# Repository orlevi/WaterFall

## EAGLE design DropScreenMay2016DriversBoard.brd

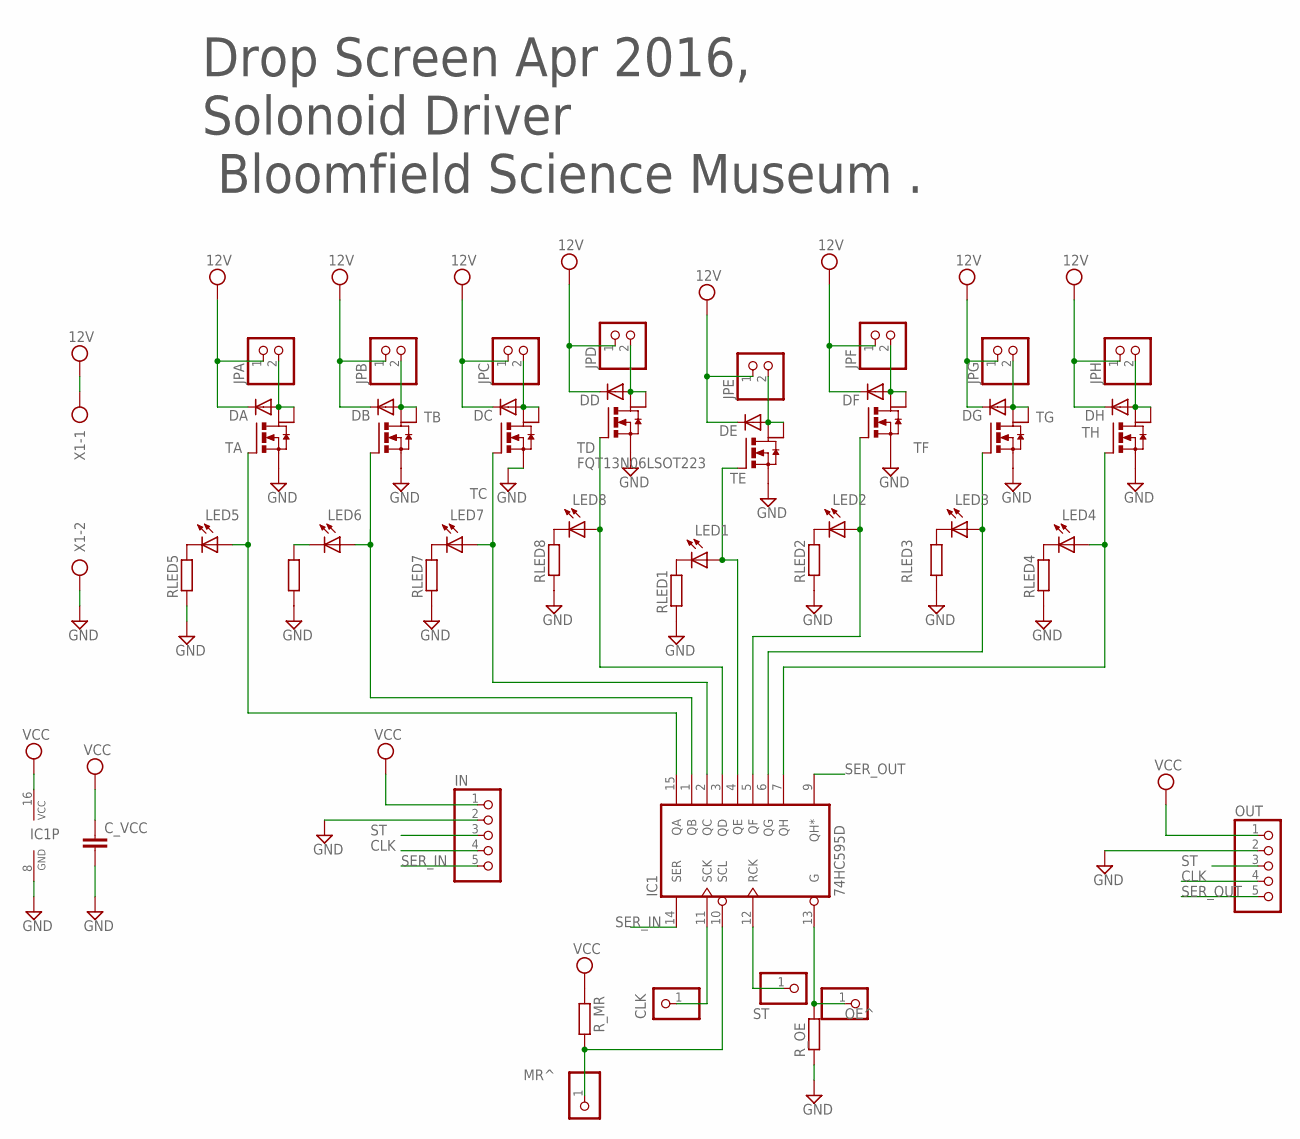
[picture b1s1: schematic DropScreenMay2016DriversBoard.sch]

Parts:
CLK, CLK1: PINHD-1X1; 1X01
C_VCC: C-EUC0805; C0805
DA: 1N4004V; DO41-25
DB: 1N4004V; DO41-25
DC: 1N4004V; DO41-25
DD: 1N4004V; DO41-25
DE: 1N4004V; DO41-25
DF: 1N4004V; DO41-25
DG: 1N4004V; DO41-25
DH: 1N4004V; DO41-25
IC1: 74HC595D; SO16
IN: PIN_HEAD_1X5_MARKEDSMAOLPAD; 1X5_MARKED_SMALL_PADS
JPA: PINHD-1X2SQ&RND; 1X02_SQ&ROUND
JPB: PINHD-1X2SQ&RND; 1X02_SQ&ROUND
JPC: PINHD-1X2SQ&RND; 1X02_SQ&ROUND
JPD: PINHD-1X2SQ&RND; 1X02_SQ&ROUND
JPE: PINHD-1X2SQ&RND; 1X02_SQ&ROUND
JPF: PINHD-1X2SQ&RND; 1X02_SQ&ROUND
JPG: PINHD-1X2SQ&RND; 1X02_SQ&ROUND
JPH: PINHD-1X2SQ&RND; 1X02_SQ&ROUND
LED1, LED2, LED3, LED4, LED5, LED6, LED7, LED8: LEDCHIPLED_0805; CHIPLED_0805
OE^: CLR; 1X01
OUT: PIN_HEAD_1X5_MARKEDSMAOLPAD; 1X5_MARKED_SMALL_PADS
RLED1, RLED2, RLED3, RLED4, RLED5, RLED6, RLED7, RLED8: R-EU_R0603; R0603
R_MR: R-EU_R0603; R0603
R_OE: R-EU_R0603; R0603
ST: ST; 1X01
TA: FQT13N06LSOT223; SOT223
TB: FQT13N06LSOT223; SOT223
TC: FQT13N06LSOT223; SOT223
TD: FQT13N06LSOT223; SOT223
TE: FQT13N06LSOT223; SOT223
TF: FQT13N06LSOT223; SOT223
TG: FQT13N06LSOT223; SOT223
TH: FQT13N06LSOT223; SOT223
X1: AK300/2

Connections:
12V: DA.C, DB.C, DC.C, DD.C, DE.C, DF.C, DG.C, DH.C, JPA.1, JPB.1, JPC.1, JPD.1, JPE.1, JPF.1, JPG.1, JPH.1, X1.1
+5V: C_VCC.1, IC1.16 (VCC), IN.1, OUT.1, R_MR.1
CLK: CLK.1, IC1.11 (SCK), IN.4, OUT.4
GND: C_VCC.2, IC1.8 (GND), IN.2, OUT.2, RLED1.1, RLED2.1, RLED3.1, RLED4.1, RLED5.1, RLED6.1, RLED7.1, RLED8.1, R_OE.1, TA.3 (S), TB.3 (S), TC.3 (S), TD.3 (S), TE.3 (S), TF.3 (S), TG.3 (S), TH.3 (S), X1.2
MR^: CLK1.1, IC1.10 (SCL), R_MR.2
unnamed: IC1.4 (QE), LED1.A, TE.1 (G)
unnamed: DE.A, JPE.2, TE.2 (D), TE.4 (D1)
unnamed: LED1.C, RLED1.2
unnamed: DF.A, JPF.2, TF.2 (D), TF.4 (D1)
unnamed: DG.A, JPG.2, TG.2 (D), TG.4 (D1)
unnamed: LED2.C, RLED2.2
unnamed: DH.A, JPH.2, TH.2 (D), TH.4 (D1)
unnamed: DA.A, JPA.2, TA.2 (D), TA.4 (D1)
unnamed: LED5.C, RLED5.2
unnamed: LED4.C, RLED4.2
unnamed: DB.A, JPB.2, TB.2 (D), TB.4 (D1)
unnamed: DD.A, JPD.2, TD.2 (D), TD.4 (D1)
unnamed: LED6.C, RLED6.2
unnamed: LED3.C, RLED3.2
unnamed: LED7.C, RLED7.2
unnamed: DC.A, JPC.2, TC.2 (D), TC.4 (D1)
unnamed: LED8.C, RLED8.2
OE^: IC1.13 (G), OE^.1, R_OE.2
QA: IC1.15 (QA), LED5.A, TA.1 (G)
QB: IC1.1 (QB), LED6.A, TB.1 (G)
QC: IC1.2 (QC), LED7.A, TC.1 (G)
QD: IC1.3 (QD), LED8.A, TD.1 (G)
QF: IC1.5 (QF), LED2.A, TF.1 (G)
QG: IC1.6 (QG), LED3.A, TG.1 (G)
QH: IC1.7 (QH), LED4.A, TH.1 (G)
SER_IN: IC1.14 (SER), IN.5
SER_OUT: IC1.9 (QH*), OUT.5
ST: IC1.12 (RCK), IN.3, OUT.3, ST.1

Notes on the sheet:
Drop Screen Apr 2016, Solonoid Driver Bloomfield Science Museum .

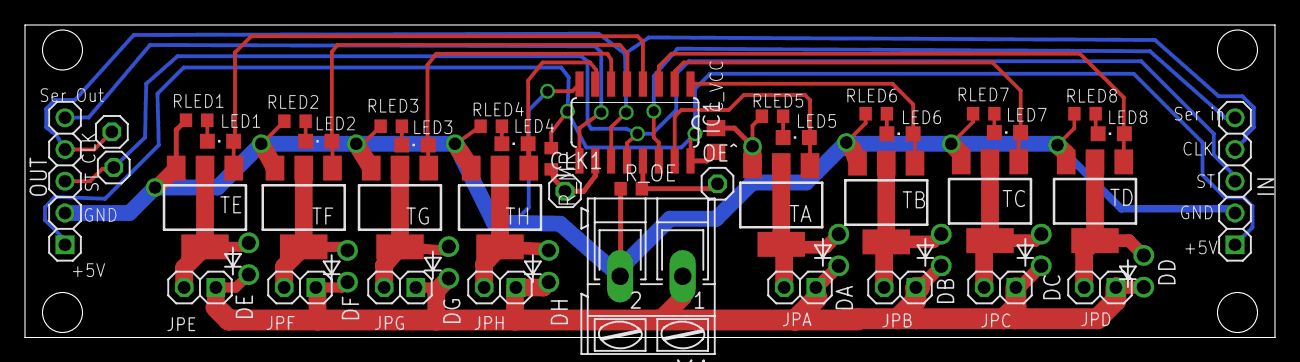
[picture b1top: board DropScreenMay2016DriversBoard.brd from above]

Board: 2 copper layers, 100.0 x 25.0 mm, 51 parts (0 on the bottom side), 33 nets.

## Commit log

2016-09-29 waterfall basic code
2017-01-05 added schematics files
2017-01-12 added some patterns
2017-01-19 [Omer] add python for image conversion
